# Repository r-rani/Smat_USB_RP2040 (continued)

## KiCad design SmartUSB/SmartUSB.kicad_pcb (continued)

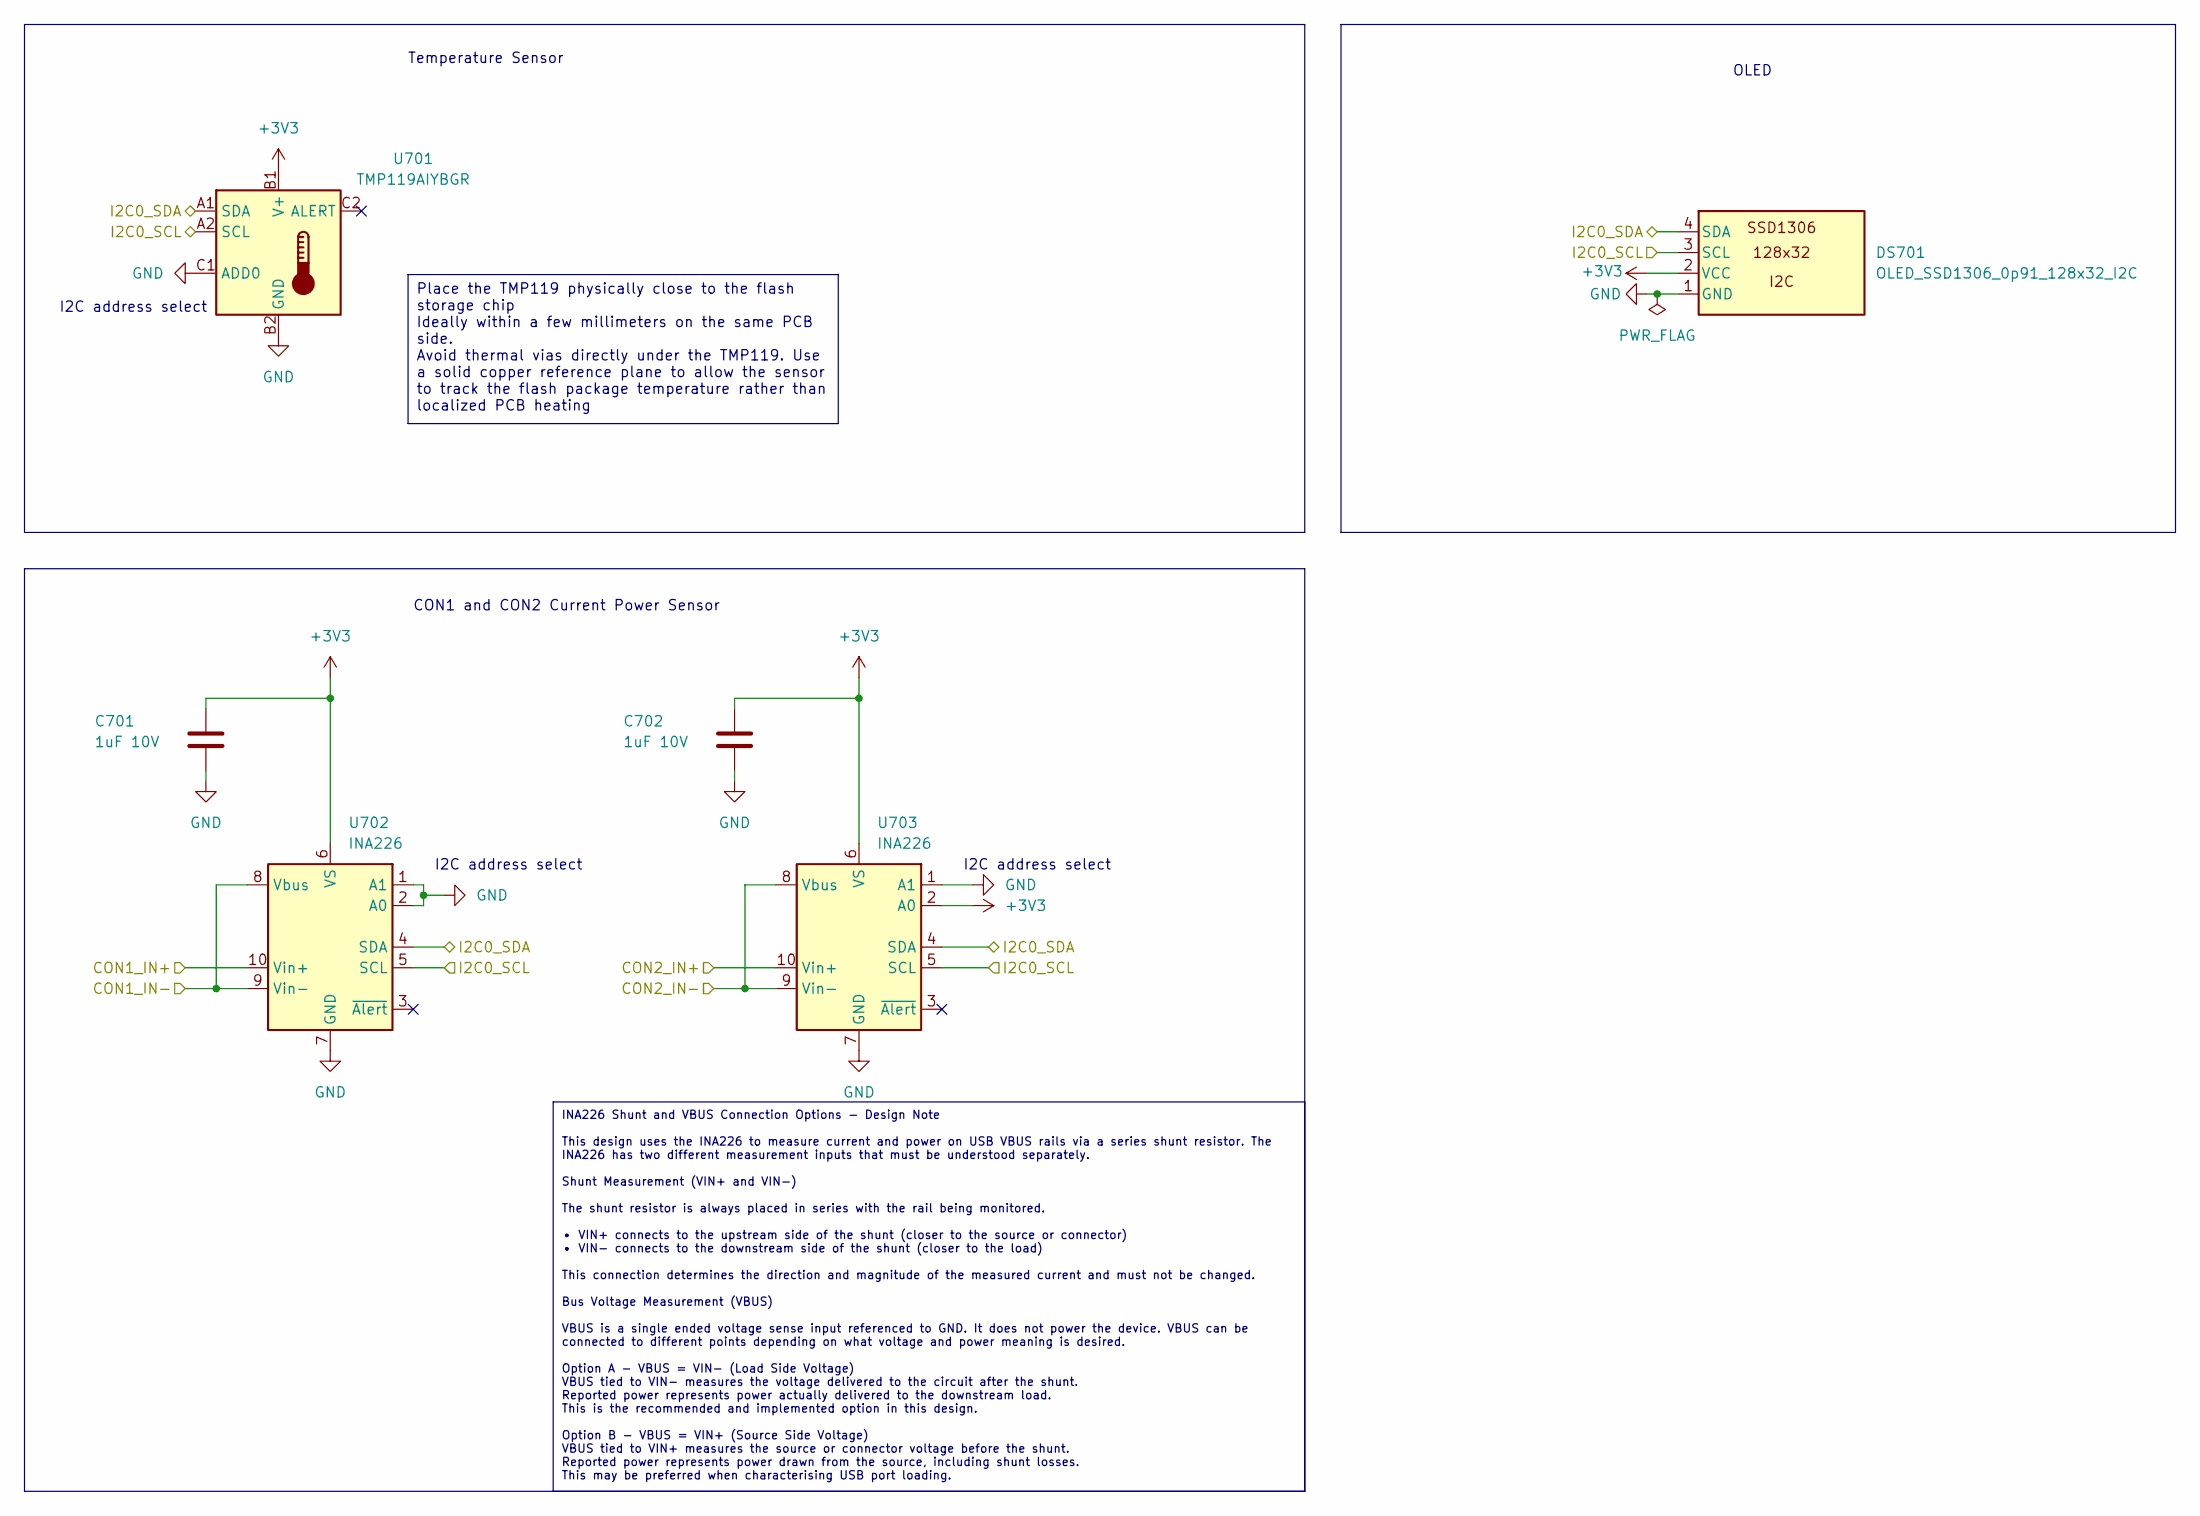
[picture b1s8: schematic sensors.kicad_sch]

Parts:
C701, C702: 1uF 10V; C_0603_1608Metric
DS701: OLED_SSD1306_0p91_128x32_I2C; SSD1306-0.91-OLED-4pin-128x32
U701: TMP119AIYBGR; Texas_DSBGA-6_0.95x1.488mm_Layout2x3_P0.4mm
U702, U703: INA226; TSSOP-10_3x3mm_P0.5mm

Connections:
+3V3: C701.1, C702.1, DS701.2 (VCC), U701.B1 (V+), U702.6 (VS), U703.2 (A0), U703.6 (VS); also elsewhere on the board
/RP2040/I2C0_SCL: DS701.3 (SCL), U701.A2 (SCL), U702.5 (SCL), U703.5 (SCL); also elsewhere on the board
/RP2040/I2C0_SDA: DS701.4 (SDA), U701.A1 (SDA), U702.4 (SDA), U703.4 (SDA); also elsewhere on the board
/VBUS_MCU: U703.8 (Vbus), U703.9 (Vin-); also elsewhere on the board
/VBUS_MCU_pre_shunt_IN+: U703.10 (Vin+); also elsewhere on the board
/VBUS_STORAGE: U702.8 (Vbus), U702.9 (Vin-); also elsewhere on the board
/VBUS_STORAGE_pre_shunt_IN+: U702.10 (Vin+); also elsewhere on the board
GND: C701.2, C702.2, DS701.1 (GND), U701.B2 (GND), U701.C1 (ADD0), U702.1 (A1), U702.2 (A0), U702.7 (GND), U703.1 (A1), U703.7 (GND); also elsewhere on the board

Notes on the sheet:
CON1 and CON2 Current Power Sensor
Temperature Sensor
OLED
I2C address select
Place the TMP119 physically close to the flash storage chip Ideally within a few millimeters on the same PCB side. Avoid thermal vias directly under the TMP119. Use a solid copper reference plane to allow the sensor to track the flash package temperature rather than localized PCB heating
INA226 Shunt and VBUS Connection Options - Design Note This design uses the INA226 to measure current and power on USB VBUS rails via a series shunt resistor. The INA226 has two different measurement inputs that must be understood separately. Shunt Measurement (VIN+ and VIN−) The shunt resistor is 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

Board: 4 copper layers, 130 parts (0 on the bottom side), 80 nets, no tracks yet.
